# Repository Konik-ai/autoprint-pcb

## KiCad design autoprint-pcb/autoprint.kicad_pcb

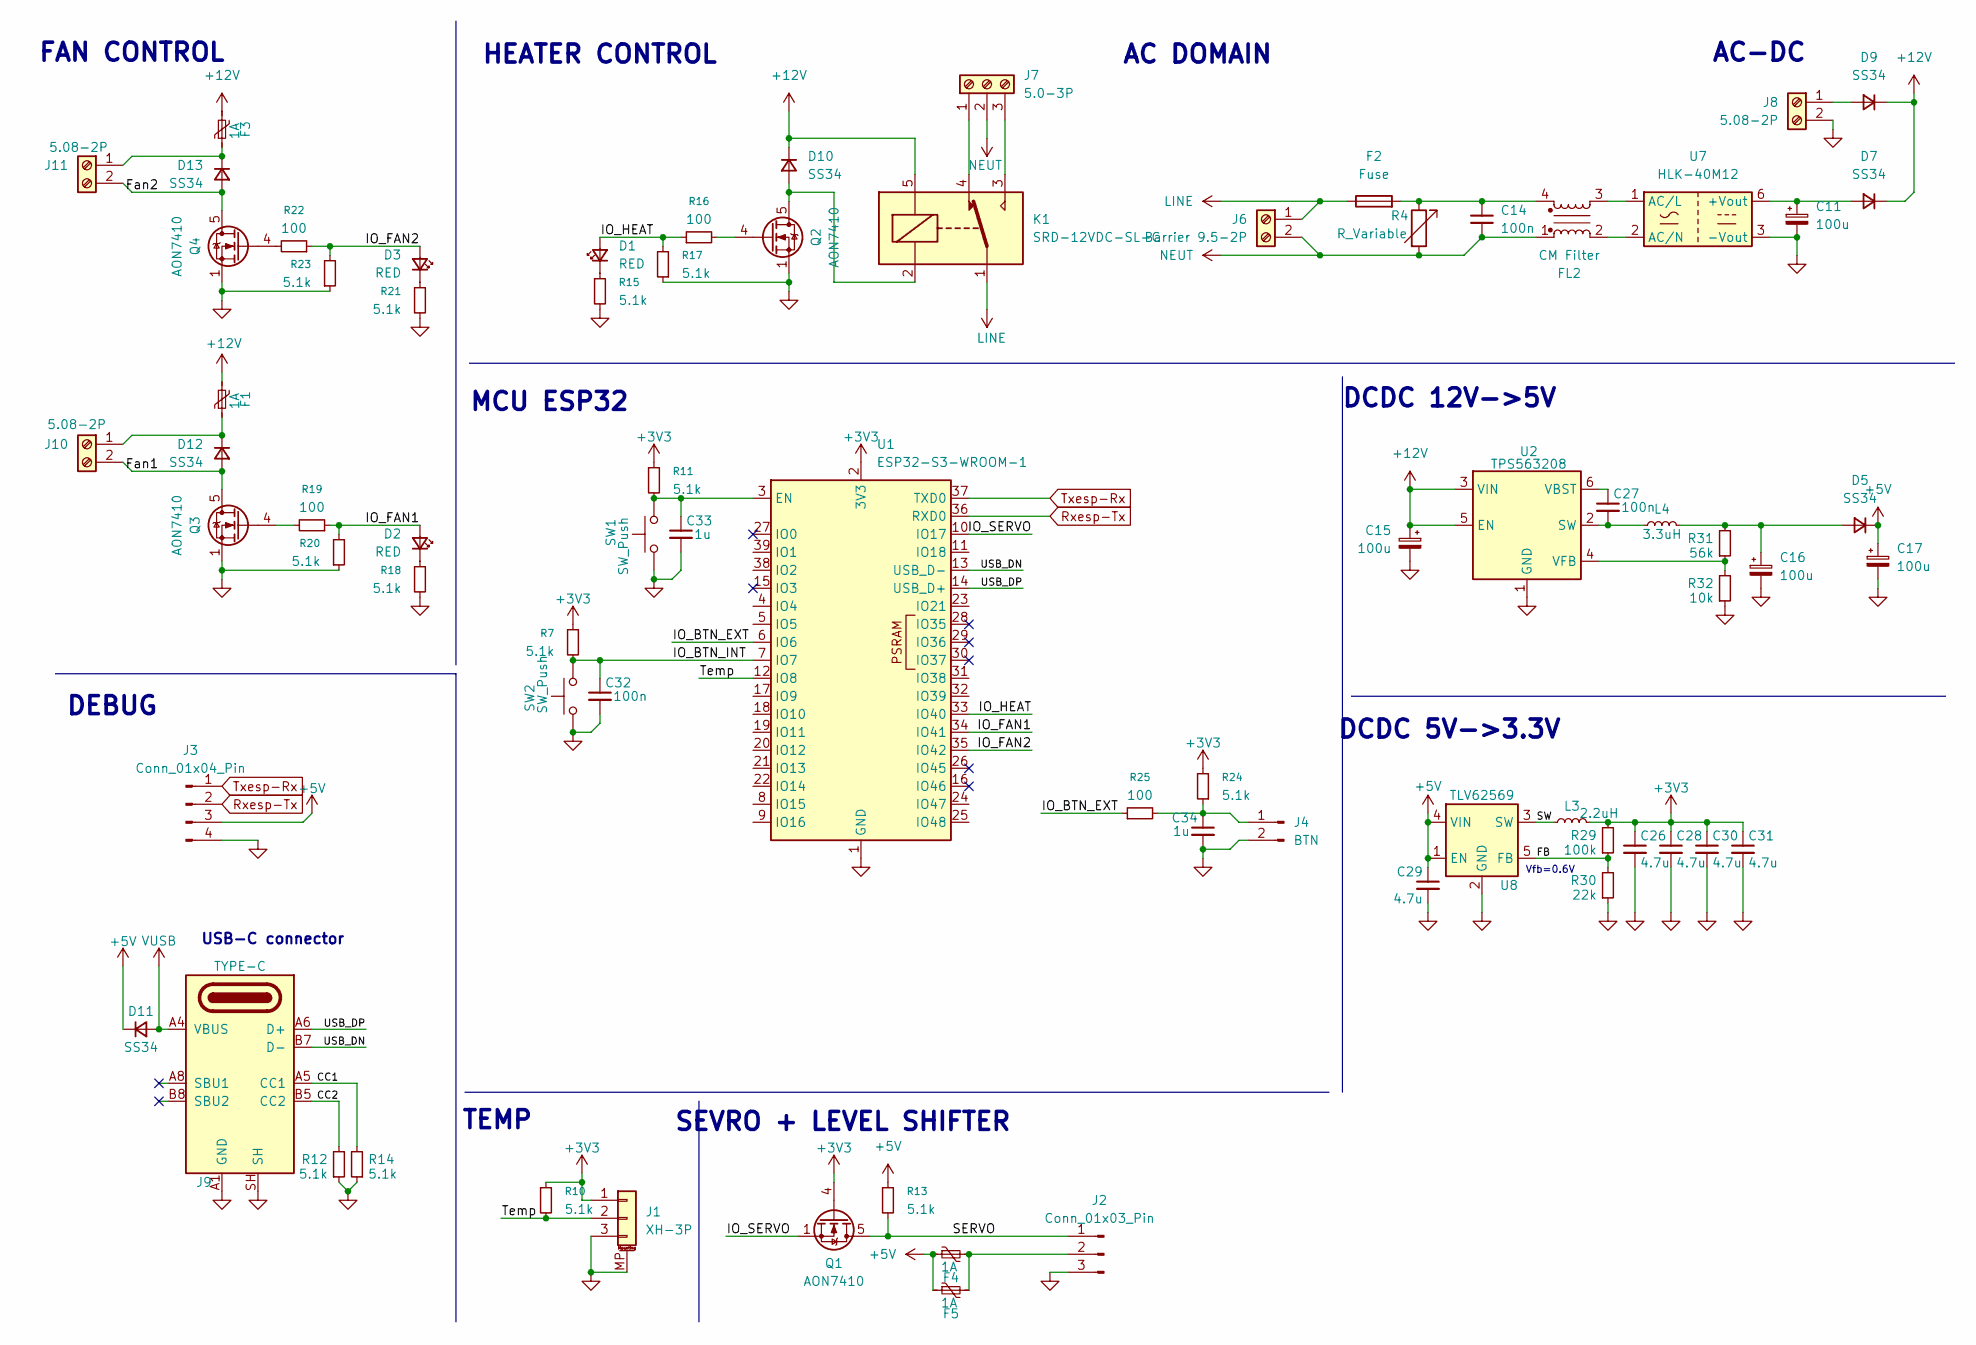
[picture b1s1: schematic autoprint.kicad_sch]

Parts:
C11, C15, C16, C17: 100u; CP_Elec_6.3x7.7; LCSC Part # C48970646
C14: 100n; C_Rect_L13.0mm_W5.0mm_P10.00mm_FKS3_FKP3_MKS4; LCSC Part # C2888214
C26, C28, C29, C30, C31: 4.7u; C_0603_1608Metric; Part Type Basic; LCSC Part # C19666
C27, C32: 100n; C_0402_1005Metric; Part Type Basic; LCSC Part # C100072
C33, C34: 1u; C_0402_1005Metric; Part Type Basic; LCSC Part # C29266
D1, D2, D3: RED; LED_0603_1608Metric; LCSC Part # C2286
D5, D7, D9, D10, D11, D12, D13: SS34; D_SMA; LCSC Part # C8678
F1, F3, F4, F5: 1A; Fuse_0805_2012Metric; LCSC Part # C22363531
F2: Fuse; Fuseholder_Cylinder-5x20mm_Stelvio-Kontek_PTF78_Horizontal_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; LCSC Part # C717030
FL2: CM Filter; L_CommonMode_PulseElectronics_PH9455x705NL_1; LCSC Part # C7498917
J1: XH-3P; JST_XH_S3B-XH-SM4-TB_1x03-1MP_P2.50mm_Horizontal; LCSC Part # C2905025
J2: Conn_01x03_Pin; PinHeader_1x03_P2.54mm_Horizontal; LCSC Part # C5383096
J3: Conn_01x04_Pin; PinHeader_1x04_P2.54mm_Vertical; LCSC Part # C5383113
J4: BTN; PinHeader_1x02_P2.54mm_Horizontal; LCSC Part # C49569548
J6: Barrier 9.5-2P; TerminalBlock_Ningbo-Kagnex_HB9500M_1x02_P9.5mm; LCSC Part # C601239
J7: 5.0-3P; TerminalBlock_Phoenix_PT-1,5-3-5.0-H_1x03_P5.00mm_Horizontal; LCSC Part # C49291884
J8, J10, J11: 5.08-2P; TerminalBlock_MaiXu_MX126-5.0-02P_1x02_P5.00mm; LCSC Part # C49291901
J9: TYPE-C; USB_C_Receptacle_HRO_TYPE-C-31-M-12; LCSC Part # C165948
K1: SRD-12VDC-SL-C; Relay_SPDT_SANYOU_SRD_Series_Form_C; LCSC Part # C30431
L3: 2.2uH; L_0603_1608Metric; Part Type Extended; LCSC Part # C337911
L4: 3.3uH; L_APV_ANR8065; Part Type Extended; LCSC Part # C55562596
Q1, Q2, Q3, Q4: AON7410; Diodes_PowerDI3333-8; LCSC Part # C269266
R4: R_Variable; RV_Disc_D12mm_W7.9mm_P7.5mm; LCSC Part # C113236
R7, R10, R11, R12, R13, R14, R15, R17, R18, R20, R21, R23, R24: 5.1k; R_0402_1005Metric; LCSC Part # C25905
R16, R19, R22, R25: 100; R_0402_1005Metric; LCSC Part # C25076
R29: 100k; R_0402_1005Metric; Part Type Basic; LCSC Part # C25741
R30: 22k; R_0402_1005Metric; Part Type Basic; LCSC Part # C25768
R31: 56k; R_0402_1005Metric; Part Type Basic; LCSC Part # C2906875
R32: 10k; R_0402_1005Metric; Part Type Basic; LCSC Part # C2906861
SW1, SW2: SW_Push; SW_Push_SPST_NO_Alps_SKRK; LCSC Part # C49234121
U1: ESP32-S3-WROOM-1; LCSC Part # C2913199
U2: TPS563208; SOT-23-6; LCSC Part # C468250
U7: HLK-40M12; Converter_ACDC_Hi-Link_HLK-30Mxx; LCSC Part # C2761169
U8: TLV62569; SOT-23-5; LCSC Part # C141836

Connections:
+3V3: C26.1, C28.1, C30.1, C31.1, J1.1, L3.2, Q1.4 (G), R7.1, R10.1, R11.1, R24.2, R29.2, U1.2 (3V3)
+5V: C17.1, C29.1, D5.1 (K), D11.1 (K), F4.1, F5.1, J3.3, R13.1, U8.1 (EN), U8.4 (VIN)
+12V: C15.1, D7.1 (K), D9.1 (K), D10.1 (K), F1.2, F3.2, K1.5, U2.3 (VIN), U2.5 (EN)
/CC1: J9.A5 (CC1), R14.2
/CC2: J9.B5 (CC2), R12.2
/FB: R29.1, R30.2, U8.5 (FB)
/Fan1: D12.2 (A), J10.2, Q3.5 (D)
/Fan2: D13.2 (A), J11.2, Q4.5 (D)
/IO_BTN_EXT: R25.1, U1.6 (IO6)
/IO_BTN_INT: C32.1, R7.2, SW2.1, U1.7 (IO7)
/IO_FAN1: D2.2 (A), R19.1, R20.2, U1.34 (IO41)
/IO_FAN2: D3.2 (A), R22.1, R23.2, U1.35 (IO42)
/IO_HEAT: D1.2 (A), R16.1, R17.2, U1.33 (IO40)
/IO_SERVO: Q1.1 (S), Q1.2 (S), Q1.3 (S), U1.10 (IO17)
/SERVO: J2.1, Q1.5 (D), R13.2
/SW: L3.1, U8.3 (SW)
/Temp: J1.2, R10.2, U1.12 (IO8)
/USB_DN: J9.A7 (D-), J9.B7 (D-), U1.13 (USB_D-)
/USB_DP: J9.A6 (D+), J9.B6 (D+), U1.14 (USB_D+)
GND: C11.2, C15.2, C16.2, C17.2, C26.2, C28.2, C29.2, C30.2, C31.2, C32.2, C33.2, C34.2, J1.3, J1.MP (MountPin), J2.3, J3.4, J4.2, J8.2, J9.A1 (GND), J9.A12 (GND), J9.B1 (GND), J9.B12 (GND), J9.SH, Q2.1 (S), Q2.2 (S), Q2.3 (S), Q3.1 (S), Q3.2 (S), Q3.3 (S), Q4.1 (S), Q4.2 (S), Q4.3 (S), R12.1, R14.1, R15.2, R17.1, R18.2, R20.1, R21.2, R23.1, R30.1, R32.1, SW1.1, SW2.2, U1.1 (GND), U1.40 (GND), U1.41 (GND), U2.1 (GND), U7.3 (-Vout), U8.2 (GND)
LINE: F2.1, J6.1, K1.1
NEUT: C14.2, FL2.1, J6.2, J7.2, R4.2
unnamed: C14.1, F2.2, FL2.4, R4.1
unnamed: D1.1 (K), R15.1
unnamed: D2.1 (K), R18.1
unnamed: D3.1 (K), R21.1
unnamed: C16.1, D5.2 (A), L4.2, R31.2
unnamed: C11.1, D7.2 (A), U7.6 (+Vout)
unnamed: D9.2 (A), J8.1
unnamed: D10.2 (A), K1.2, Q2.5 (D)
unnamed: D12.1 (K), F1.1, J10.1
unnamed: D13.1 (K), F3.1, J11.1
unnamed: F4.2, F5.2, J2.2
unnamed: C34.1, J4.1, R24.1, R25.2
unnamed: J7.1, K1.4
unnamed: J7.3, K1.3
unnamed: Q2.4 (G), R16.2
unnamed: Q3.4 (G), R19.2
unnamed: Q4.4 (G), R22.2
unnamed: C33.1, R11.2, SW1.2, U1.3 (EN)
unnamed: C27.2, L4.1, U2.2 (SW)
unnamed: C27.1, U2.6 (VBST)
unnamed: R31.1, R32.2, U2.4 (VFB)
unnamed: FL2.3, U7.1 (AC/L)
unnamed: FL2.2, U7.2 (AC/N)
Rxesp-Tx: J3.2, U1.36 (RXD0)
Txesp-Rx: J3.1, U1.37 (TXD0)
VUSB: D11.2 (A), J9.A4 (VBUS), J9.A9 (VBUS), J9.B4 (VBUS), J9.B9 (VBUS)

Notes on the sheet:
TEMP
USB-C connector
AC-DC
FAN CONTROL
Vfb=0.6V
SEVRO + LEVEL SHIFTER
AC DOMAIN
MCU ESP32
DCDC 5V->3.3V
DCDC 12V->5V
DEBUG
HEATER CONTROL

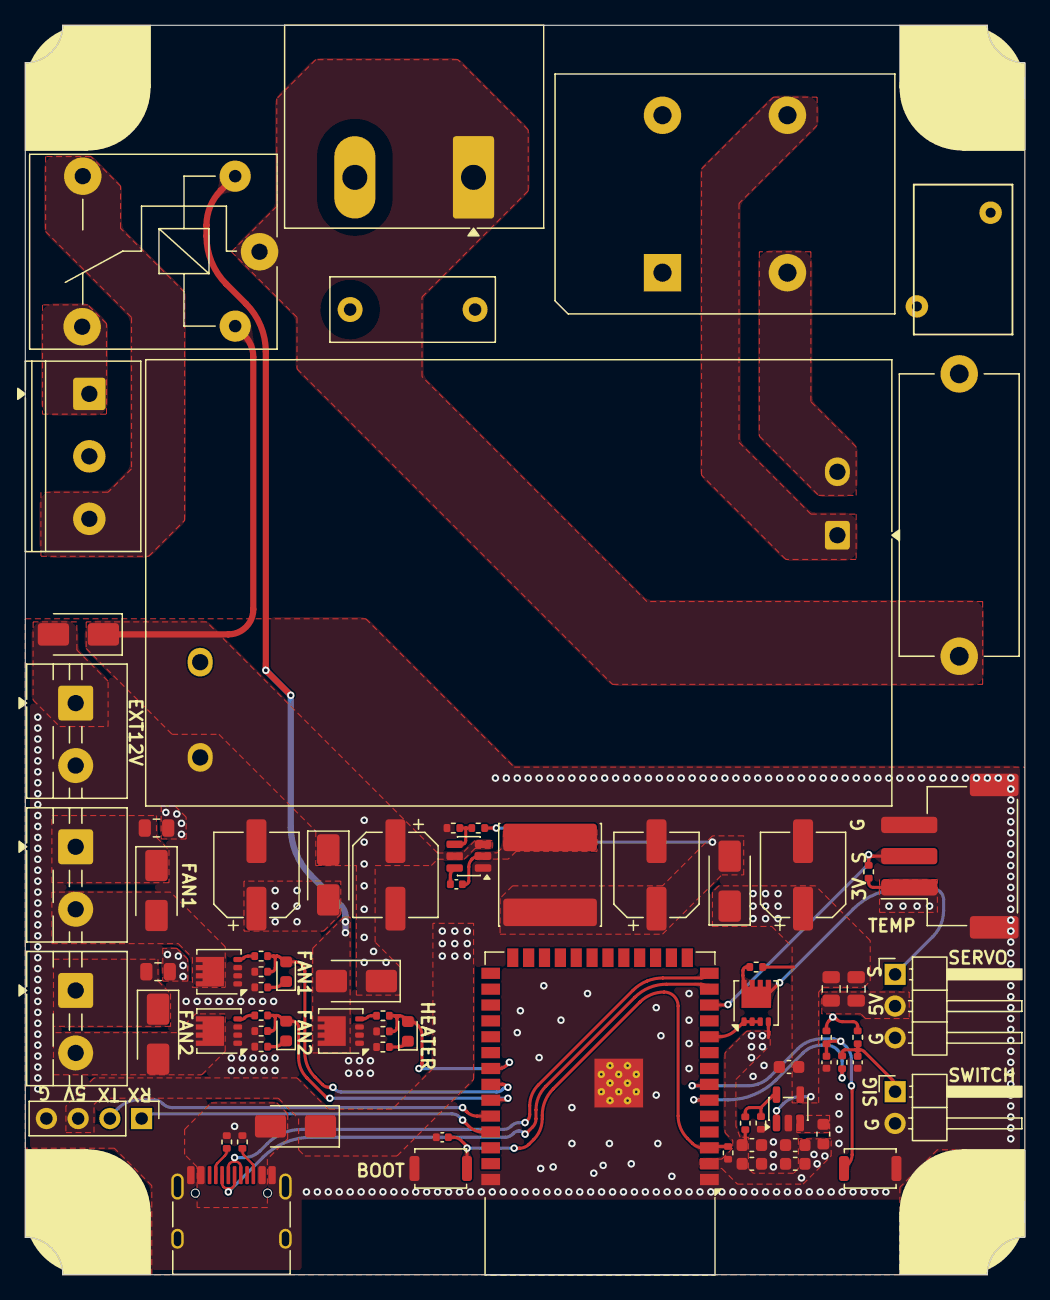
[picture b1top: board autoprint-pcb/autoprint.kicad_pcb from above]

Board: 2 copper layers, 80.0 x 100.0 mm, 75 parts (0 on the bottom side), 48 nets.

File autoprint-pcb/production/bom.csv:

Designator,Footprint,Quantity,Value,LCSC Part #
"C11, C15, C16, C17",CP_Elec_6.3x7.7,4,100u,C48970646
C14,C_Rect_L13.0mm_W5.0mm_P10.00mm_FKS3_FKP3_MKS4,1,100n,C2888214
"C26, C28, C29, C30, C31",0603,5,4.7u,C19666
"C27, C32",0402,2,100n,C100072
"C33, C34",0402,2,1u,C29266
"D1, D2, D3",0603,3,RED,C2286
"D10, D11, D12, D13, D5, D7, D9",D_SMA,7,SS34,C8678
"F1, F3, F4, F5",0805,4,1A,C22363531
F2,Fuseholder_Cylinder-5x20mm_Stelvio-Kontek_PTF78_Horizontal_Open,1,Fuse,C717030
FL2,L_CommonMode_PulseElectronics_PH9455x705NL_1,1,CM Filter,C7498917
J1,JST_XH_S3B-XH-SM4-TB_1x03-1MP_P2.50mm_Horizontal,1,XH-3P,C2905025
"J10, J11, J8",TerminalBlock_MaiXu_MX126-5.0-02P_1x02_P5.00mm,3,5.08-2P,C49291901
J2,PinHeader_1x03_P2.54mm_Horizontal,1,Conn_01x03_Pin,C5383096
J3,PinHeader_1x04_P2.54mm_Vertical,1,Conn_01x04_Pin,C5383113
J4,PinHeader_1x02_P2.54mm_Horizontal,1,BTN,C49569548
J6,TerminalBlock_Ningbo-Kagnex_HB9500M_1x02_P9.5mm,1,Barrier 9.5-2P,C601239
J7,"TerminalBlock_Phoenix_PT-1,5-3-5.0-H_1x03_P5.00mm_Horizontal",1,5.0-3P,C49291884
J9,USB_C_Receptacle_HRO_TYPE-C-31-M-12,1,TYPE-C,C165948
K1,Relay_SPDT_SANYOU_SRD_Series_Form_C,1,SRD-12VDC-SL-C,C30431
L3,0603,1,2.2uH,C337911
L4,L_APV_ANR8065,1,3.3uH,C55562596
"Q1, Q2, Q3, Q4",Diodes_PowerDI3333-8,4,AON7410,C269266
"R10, R11, R12, R13, R14, R15, R17, R18, R20, R21, R23, R24, R7",0402,13,5.1k,C25905
"R16, R19, R22, R25",0402,4,100,C25076
R29,0402,1,100k,C25741
R30,0402,1,22k,C25768
R31,0402,1,56k,C2906875
R32,0402,1,10k,C2906861
R4,RV_Disc_D12mm_W7.9mm_P7.5mm,1,R_Variable,C113236
"SW1, SW2",SW_Push_SPST_NO_Alps_SKRK,2,SW_Push,C49234121
U1,ESP32-S3-WROOM-1,1,ESP32-S3-WROOM-1,C2913199
U2,SOT-23-6,1,TPS563208,C468250
U7,Converter_ACDC_Hi-Link_HLK-30Mxx,1,HLK-40M12,C2761169
U8,SOT-23-5,1,TLV62569,C141836

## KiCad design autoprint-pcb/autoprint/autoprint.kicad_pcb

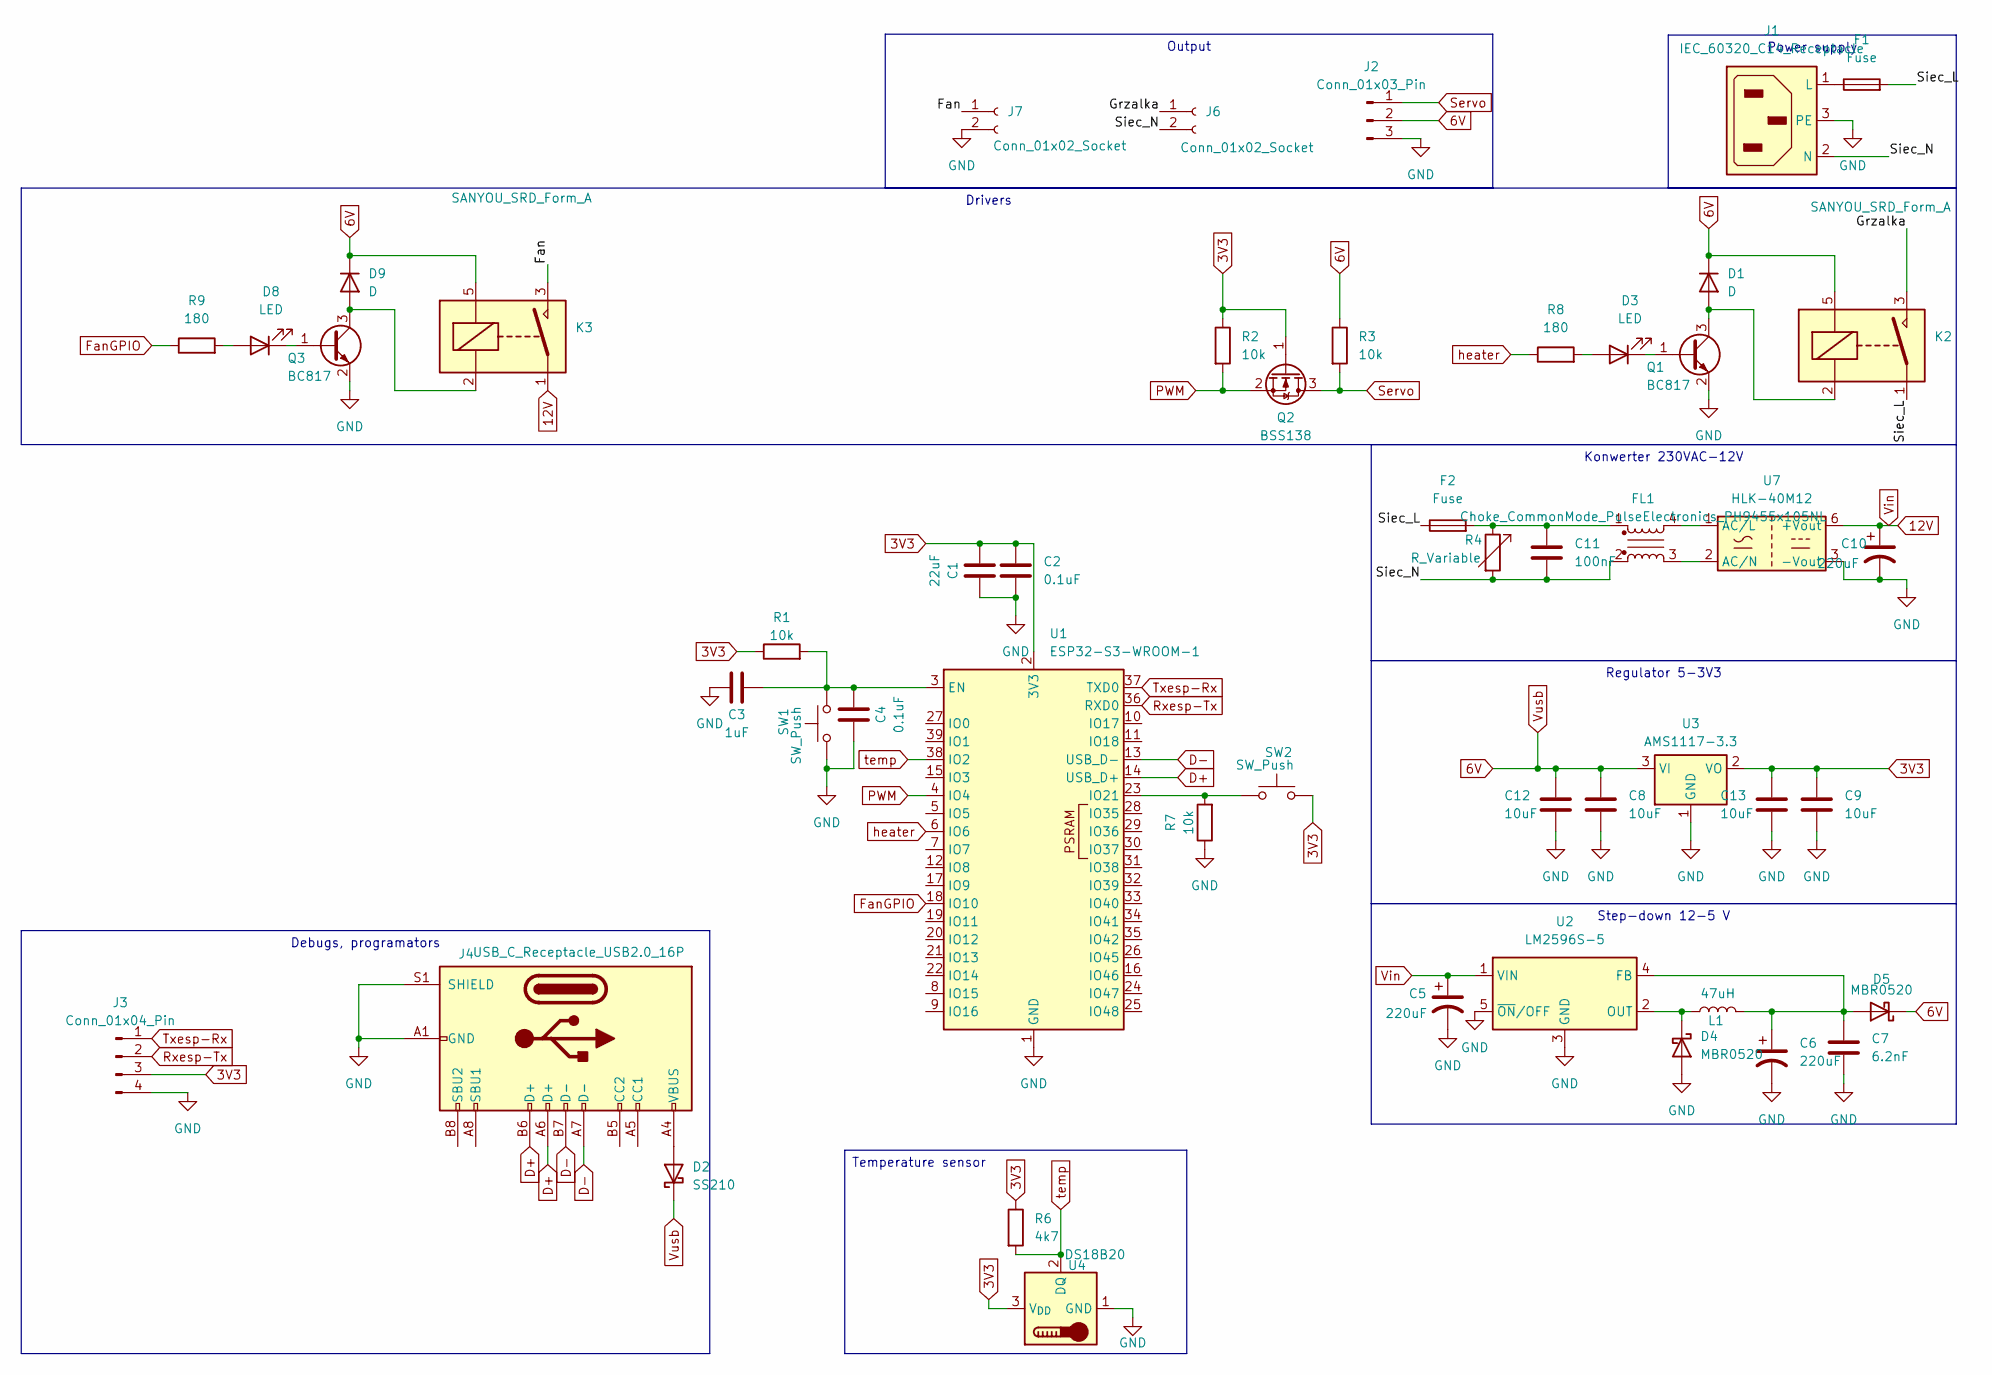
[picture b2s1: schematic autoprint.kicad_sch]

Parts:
C1: 22uF; C_0603_1608Metric
C2, C4: 0.1uF; C_0402_1005Metric
C3: 1uF; C_0402_1005Metric
C5, C6, C10: 220uF; CP_Radial_D16.0mm_P7.50mm
C7: 6.2nF; C_0603_1608Metric
C8, C9, C12, C13: 10uF; CP_EIA-3216-18_Kemet-A_HandSolder
C11: 100nF; C_Disc_D10.5mm_W5.0mm_P10.00mm
D1, D9: D; D_SOD-123
D2: SS210; D_SMA
D3, D8: LED; LED_0805_2012Metric
D4, D5: MBR0520; SOD-123FL
F1, F2: Fuse; Fuseholder_Cylinder-5x20mm_Schurter_0031_8201_Horizontal_Op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
FL1: Choke_CommonMode_PulseElectronics_PH9455x105NL; L_CommonMode_PulseElectronics_PH9455x705NL_1
J1: IEC_60320_C14_Receptacle; RT-C14-C0B-AA
J2: Conn_01x03_Pin; PinHeader_1x03_P2.54mm_Vertical
J3: Conn_01x04_Pin; PinHeader_1x04_P2.54mm_Vertical
J4: USB_C_Receptacle_USB2.0_16P; USB_C_Receptacle_Palconn_UTC16-G
J6, J7: Conn_01x02_Socket; TerminalBlock_MaiXu_MX126-5.0-02P_1x02_P5.00mm
K2, K3: SANYOU_SRD_Form_A; Relay_SPST_SANYOU_SRD_Series_Form_A
L1: 47uH; L_Sunlord_MWSA1003S
Q1, Q3: BC817; SOT-23
Q2: BSS138; SOT-23
R1, R2, R3, R7: 10k; R_0805_2012Metric
R4: R_Variable; RV_Disc_D12mm_W7.9mm_P7.5mm
R6: 4k7; R_0805_2012Metric
R8, R9: 180; R_0402_1005Metric
SW1, SW2: SW_Push; SW_PUSH_1P1T_6x3.5mm_H4.3_APEM_MJTP1243
U1: ESP32-S3-WROOM-1
U2: LM2596S-5; TO-263-5_TabPin3
U3: AMS1117-3.3; SOT-223-3_TabPin2
U4: DS18B20; TO-92_Inline
U7: HLK-40M12; Converter_ACDC_Hi-Link_HLK-30Mxx

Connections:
3V3: C1.1, C2.2, C9.1, C13.1, J3.3, Q2.1 (G), R1.1, R2.1, R6.1, SW2.2, U1.2 (3V3), U3.2 (VO), U4.3 (V_{DD})
6V: C8.1, C12.1, D1.1 (K), D2.1 (K), D5.C (K), D9.1 (K), J2.2, K2.5, K3.5, R3.1, U3.3 (VI)
12V: C5.1, C10.1, K3.1, U2.1 (VIN), U7.6 (+Vout)
/Fan: J7.1, K3.3
/Grzalka: J6.1, K2.3
/Siec_L: F1.2, F2.1, K2.1
/Siec_N: C11.2, FL1.2, J1.2 (N), J6.2, R4.2
D+: J4.A6 (D+), J4.B6 (D+), U1.14 (USB_D+)
D-: J4.A7 (D-), J4.B7 (D-), U1.13 (USB_D-)
FanGPIO: R9.1, U1.18 (IO10)
GND: C1.2, C2.1, C3.1, C4.1, C5.2, C6.2, C7.2, C8.2, C9.2, C10.2, C12.2, C13.2, D4.A, J1.3 (PE), J2.3, J3.4, J4.A1 (GND), J4.A12 (GND), J4.B1 (GND), J4.B12 (GND), J4.S1 (SHIELD), J7.2, Q1.2 (E), Q3.2 (E), R7.1, SW1.1, U1.1 (GND), U1.40 (GND), U1.41 (GND), U2.3 (GND), U2.5 (~ON/OFF), U3.1 (GND), U4.1 (GND), U7.3 (-Vout)
unnamed: C11.1, F2.2, FL1.1, R4.1
unnamed: D1.2 (A), K2.2, Q1.3 (C)
unnamed: D2.2 (A), J4.A4 (VBUS), J4.A9 (VBUS), J4.B4 (VBUS), J4.B9 (VBUS)
unnamed: D3.2 (A), R8.2
unnamed: D3.1 (K), Q1.1 (B)
unnamed: D4.C (K), L1.1, U2.2 (OUT)
unnamed: D8.2 (A), R9.2
unnamed: D8.1 (K), Q3.1 (B)
unnamed: D9.2 (A), K3.2, Q3.3 (C)
unnamed: F1.1, J1.1 (L)
unnamed: C3.2, C4.2, R1.2, SW1.2, U1.3 (EN)
unnamed: R7.2, SW2.1, U1.23 (IO21)
unnamed: C6.1, C7.1, D5.A, L1.2, U2.4 (FB)
unnamed: FL1.4, U7.1 (AC/L)
unnamed: FL1.3, U7.2 (AC/N)
PWM: Q2.2 (S), R2.2, U1.4 (IO4)
Rxesp-Tx: J3.2, U1.36 (RXD0)
Servo: J2.1, Q2.3 (D), R3.2
Txesp-Rx: J3.1, U1.37 (TXD0)
heater: R8.1, U1.6 (IO6)
temp: R6.2, U1.38 (IO2), U4.2 (DQ)

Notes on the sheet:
Drivers
Output
Regulator 5-3V3
Temperature sensor
Step-down 12-5 V
Power supply
Debugs, programators
Konwerter 230VAC-12V

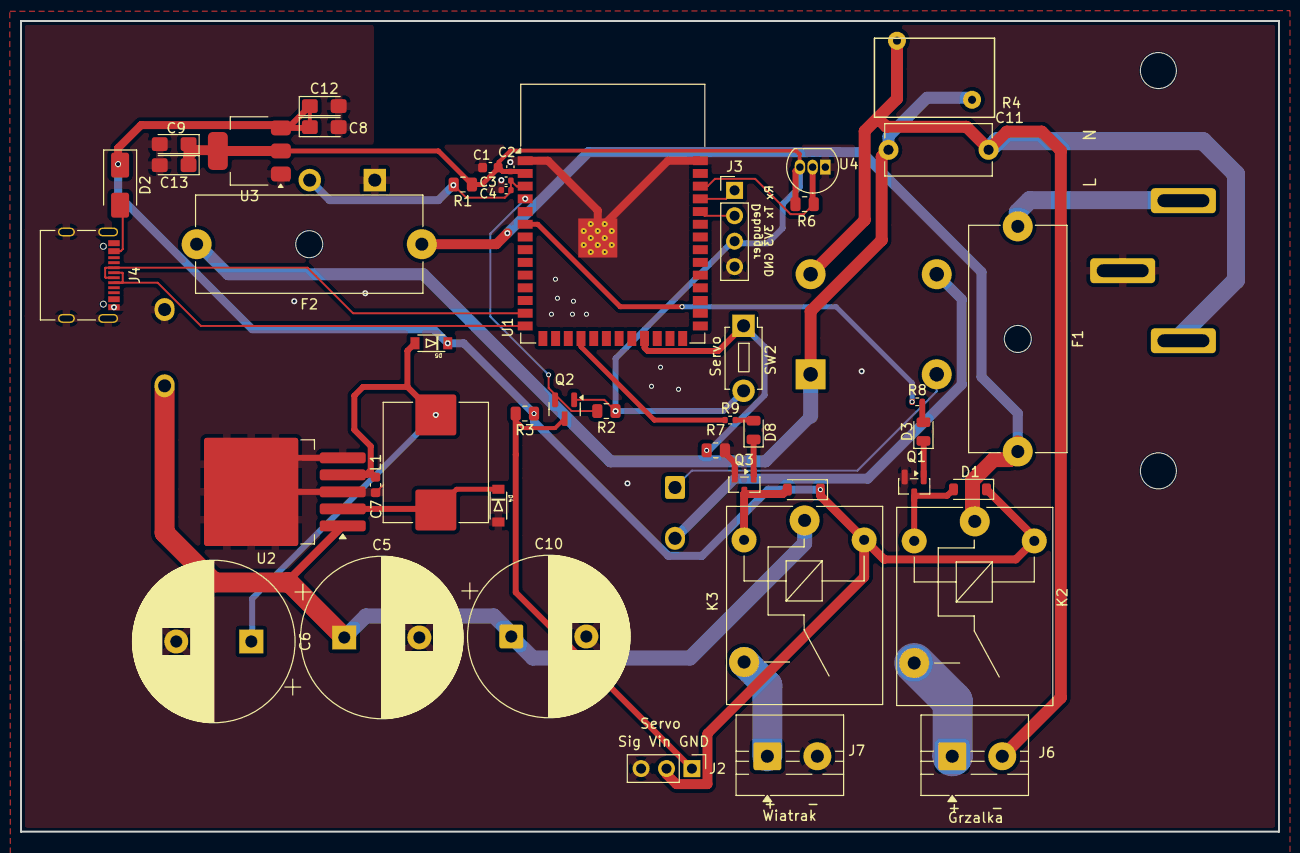
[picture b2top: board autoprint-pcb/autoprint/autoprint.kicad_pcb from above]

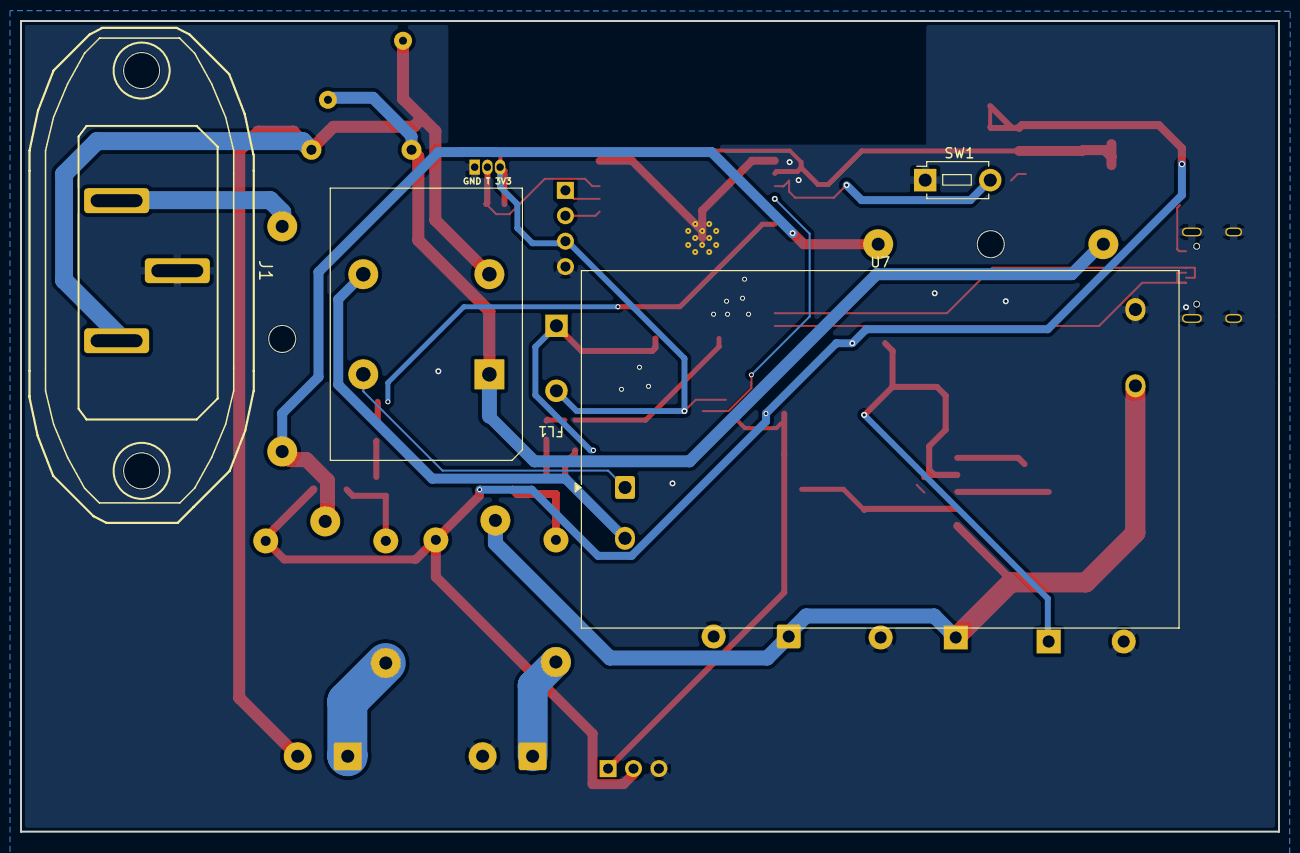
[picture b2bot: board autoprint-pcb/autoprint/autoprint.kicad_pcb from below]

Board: 2 copper layers, 125.7 x 81.0 mm, 50 parts (4 on the bottom side), 32 nets.

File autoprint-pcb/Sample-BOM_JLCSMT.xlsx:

Comment | Designator | Footprint | JLCPCB Part #（optional）
22uF | C1 |  | C59461
0.1uF | C2,C4 |  | C1525
1uF | C3 |  | C52923
220uF | C5,C6,C10 |  | C106296
6.2nF | C7 |  | C1631
10uF | C8,C9, C12, C13 |  | C7171
100nF | C11 |  | C2888214
D | D1,D9 |  | C21565
SS210 | D2 |  | C14996
LED | D3,D8 |  | C84256
MBR0520 | D4,D5 |  | C5204745
Fuse | F1,F2 |  | C3131
Choke_CommonMode_PulseElectronics_PH9455x105NL | FL1 |  | C7498917
IEC_60320_C14_Receptacle | J1 |  | C18221849
USB_C_Receptacle_USB2.0_16P | J4 |  | C2927036
Conn_01x02_Socket | J6,J7 |  | C8269
SANYOU_SRD_Form_A | K2,K3 |  | C140615
47uH | L1 |  | C149599
BC817 | Q1,Q3 |  | C2137
BSS138 | Q2 |  | C52895
10k | R1,R2,R3,R7 |  | C17414
R_Variable | R4 |  | C113236
4k7 | R6 |  | C17673
180 | R8,R9 |  | C25084
SW_Push | SW1,SW2 |  | C52037084
ESP32-S3-WROOM-1 | U1 |  | C2913199
LM2596S-5 | U2 |  | C2980820
AMS1117-3.3 | U3 |  | SOT-223-3
HLK-40M12 | U7 |  | C2761169
